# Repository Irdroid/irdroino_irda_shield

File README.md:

# Irdroino irDA Shield

The Irdroino IrDA shield is a shield for Arduino that will allow you to communicate with IrDA compiant equipment such as devices that support IrDA SIR communication up to 115200 bps (Power Meters, PDAs , data acquisition devices and other devices that communicate via IrDA SIR ).

- Compatible with Arduino UNO board layouts
- Supports with IrDA® Physical Layer Specification (version 1.3)
- High quality infrared transceiver
- Up to *5 meters IrDA SIR communication
- Supports baud rates from 9600 – 115200 bps
- Demo code that demostrates how to communicate with the Shield

### Version
1.0
### Grab a sample

You can grab a sample board from https://irdroid.eu/product/irdroino-irda-shield/

### Todos

 - n/a
 
License
----
GPL 2.0

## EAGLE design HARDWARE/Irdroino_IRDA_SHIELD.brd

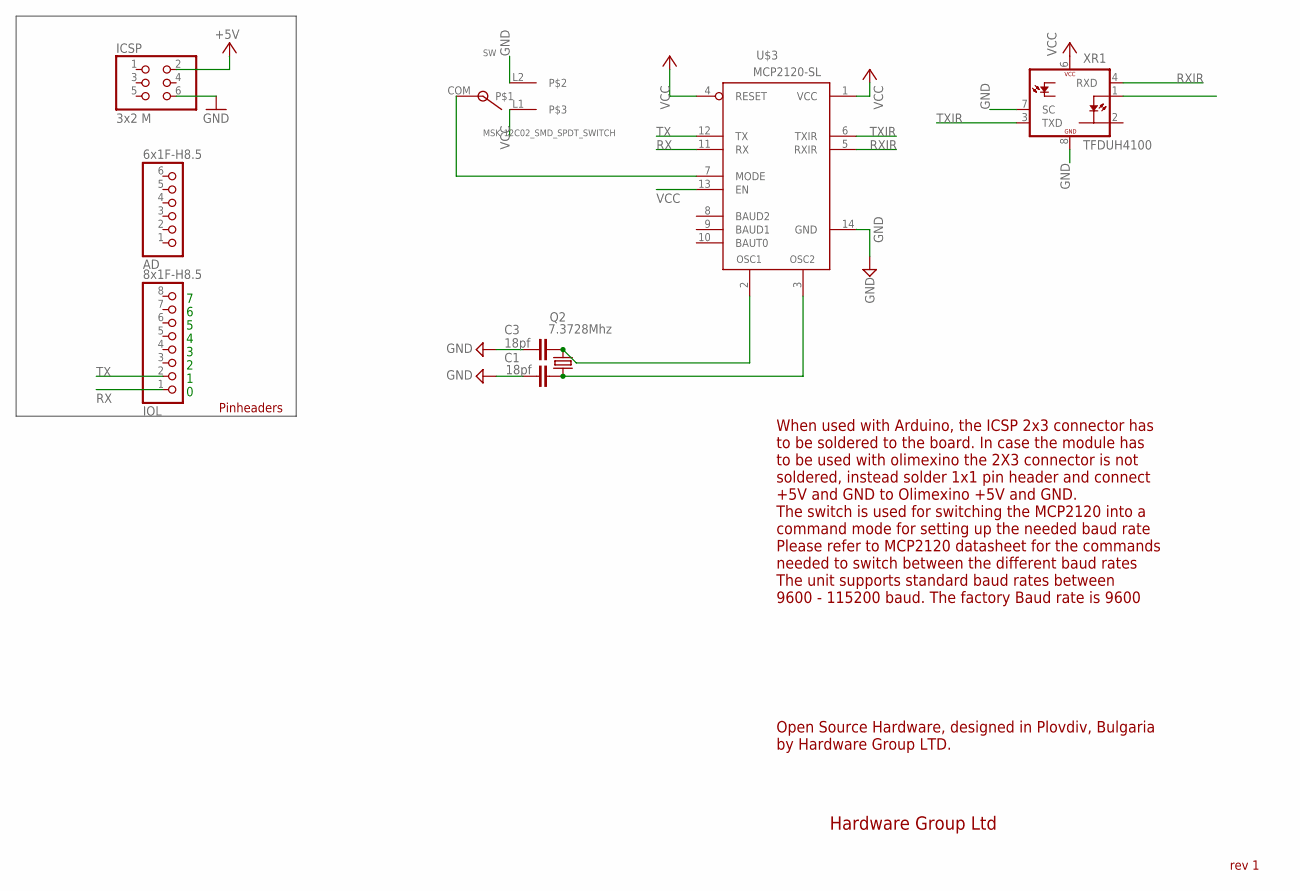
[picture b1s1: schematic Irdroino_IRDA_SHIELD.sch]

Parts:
AD: 6x1F-H8.5; 1X06
C1, C3: 18pf; C603
ICSP: 3x2 M; 2X03
IOL: 8x1F-H8.5; 1X08
Q2: 7.3728Mhz; HC49UP
SW: MSK-12C02_SMD_SPDT_SWITCH; MSK-12C02
U$3: MCP2120-SL; SO-14
XR1: TFDUH4100; TFDU4-HOR

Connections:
GND: C1.2, C3.2, ICSP.6, SW.L2, U$3.14 (GND), XR1.7 (SC), XR1.8 (GND)
unnamed: C3.1, Q2.2, U$3.2 (OSC1)
unnamed: C1.1, Q2.1, U$3.3 (OSC2)
unnamed: SW.COM, U$3.7 (MODE)
RX: IOL.1, U$3.11 (RX)
RXIR: U$3.5 (RXIR), XR1.4 (RXD)
TX: IOL.2, U$3.12 (TX)
TXIR: U$3.6 (TXIR), XR1.3 (TXD)
VCC: ICSP.2, SW.L1, U$3.1 (VCC), U$3.4 (RESET), U$3.13 (EN), XR1.1 (IRED-A), XR1.6 (VCC)

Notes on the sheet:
Pinheaders
Hardware Group Ltd
rev 1
When used with Arduino, the ICSP 2x3 connector has to be soldered to the board. In case the module has to be used with olimexino the 2X3 connector is not soldered, instead solder 1x1 pin header and connect +5V and GND to Olimexino +5V and GND. The switch is used for switching the MCP2120 into a com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
Open Source Hardware, designed in Plovdiv, Bulgaria by Hardware Group LTD.

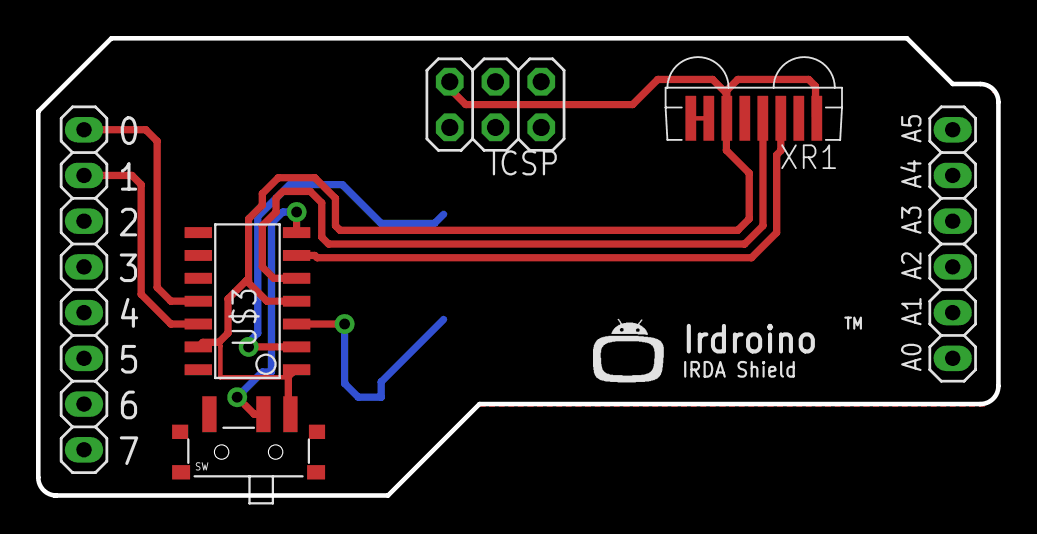
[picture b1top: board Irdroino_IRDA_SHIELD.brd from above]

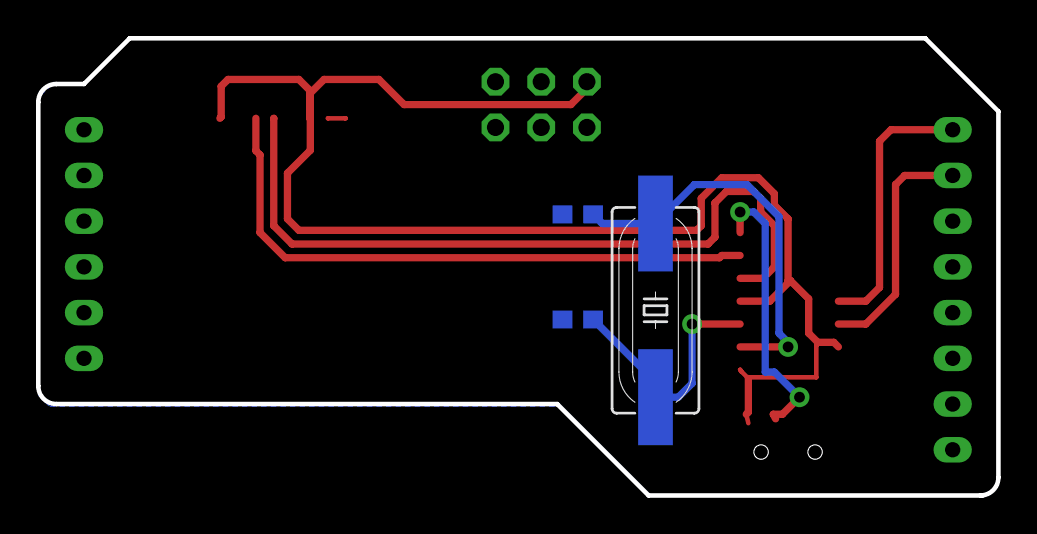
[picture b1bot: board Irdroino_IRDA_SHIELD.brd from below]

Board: 2 copper layers, 53.3 x 25.4 mm, 10 parts (3 on the bottom side), 9 nets.

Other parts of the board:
U$2: IRDROIDLOGO

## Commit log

2019-03-28 Initial Commit
    Initial Commit
2019-03-29 updated readme.md
    updated readme.md
